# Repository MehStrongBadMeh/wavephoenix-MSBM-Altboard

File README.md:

<h1 align="center">
    WavePhoenix-MSBM-Altboard
</h1>

<p align="center">
    An alternate board design for the WavePhoenix Nintendo WaveBird open-source receiver 
</p>

## Motivation

loopj's Wavephoenix receiver design relies on the RF-Star RF-BM-BG22C3 SoC, which quickly became out-of-stock everywhere, potentially due to people wanting them to make WavePhoenix receivers. So, I set out looking for an alternative. I ended up stumbling upon the [RF-BM-BG22A3](https://www.rfstariot.com/rf-bm-bg22a3-ble5-3-efr32bg22-module_p81.html) which utillizes the same SoC, in a slightly larger package. This means that, if wired properly, it could use the same firmware as the stock Wavephoenix board without modifications. All that was needed was an updated PCB design to utillize this alternate package, and a reworked case to fit the new PCB. The result is slightly bigger than the stock Wavephoenix, but still quite a bit smaller than the original Wavebird receiver.

As a bonus, the pcb antenna in the RF-BM-BG22A3 has great range. I have clocked over 40 feet of range without noticing dropouts.

## Firmware

The WavePhoenix-MSBM-Altboard is identical to the stock firmware of the WavePhoenix, [which can be found here](https://github.com/loopj/wavephoenix).

## Hardware

The hardware for the WavePhoenix-MSBM-Altboard receiver variant is available in the [`hardware/mini-receiver-msbm-altboard`](hardware/mini-receiver-msbm-altboard) directory. The receiver is similar to the reference WavePhoenix receiver other than the replacement of the RF-BM-BG22C3 with the RF-BM-BG22A3.

The hardware folder contains a simple PCB which hosts a [RF-BM-BG22A3](https://www.rfstariot.com/rf-bm-bg22a3-ble5-3-efr32bg22-module_p81.html) module, a pairing button, a status LED, and a JST connector for connecting to a GameCube controller port, as well as a 3D printable case.

- [`case`](hardware/mini-receiver-msbm-altboard/case) - 3D printable case for the receiver
- [`case-usb`](hardware/mini-receiver-msbm-altboard/case-usb) - 3D printable case for a special USB variant of the receiver
- [`gerbers`](hardware/mini-receiver-msbm-altboard/gerbers) - Gerber files for ordering the PCB
- [`KiCad`](hardware/mini-receiver-msbm-altboard/KiCad) - KiCad project files for the PCB

Check out the [`hardware/mini-receiver-msbm-altboard/README.md`](hardware/mini-receiver-msbm-altboard/README.md) for more information on how to build your own receiver based on this hardware variant.

## Special Thanks

- [loopj](https://github.com/loopj) - for creating the original WavePhoenix firmware and hardware that this variant is based on
- [dwillmore](https://github.com/dwillmore) and [unicab369](https://github.com/unicab369) - for giving me a crash course in using KiCad

## License

The hardware is licensed under the [Solderpad Hardware License v2.1](hardware/LICENSE).

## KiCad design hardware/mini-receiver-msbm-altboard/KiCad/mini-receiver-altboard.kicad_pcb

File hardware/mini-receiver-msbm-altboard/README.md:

# WavePhoenix-MSBM-Altboard Mini Receiver

The WavePhoenix-MSBM-Altboard Mini Receiver is a small, low-cost WaveBird receiver replacement based on the original WavePhoenix design. It has been designed to use an alternate chipset but otherwise function identically.

The receiver uses a cheap, off-the-shelf wireless module (the [RF-BM-BG22A3](https://www.rfstariot.com/rf-bm-bg22a3-ble5-3-efr32bg22-module_p81.html)), which can either be hand-wired, or assembled onto a custom PCB.

## Differences

Functionally identical to the stock WavePhoenix other than:

- You need 1x RF-BM-BG22A3 module ([AliExpress](https://www.aliexpress.us/item/3256801502682253.html?spm=a2g0o.detail.1000023.8.191b9Yh19Yh1qO&gatewayAdapt=glo2usa4itemAdapt), [LCSC](https://lcsc.com/product-detail/Bluetooth-Modules_RF-star-RF-BM-BG22A3_C5441203.html?s_z=n_RF-BM-BG22A3), [Tindie](https://www.tindie.com/products/rfstariot/efr32bg22-long-range-bluetooth-wireless-module/)) instead of the RF-BM-BG22C3
- The case has been designed to be used with a standard 1.6mm thick PCB instead of the 1.2mm thickness PCB the stock WavePhoenix was designed around.

## Build Guide

**This guide below is identical to the stock guide ([https://github.com/loopj/wavephoenix/tree/main/hardware/mini-receiver]), other than the differences listed above and some other minor additions**

### Parts

- Assembled Mini Receiver PCB - (see [PCB](#pcb))
- 3D printed case - (see [Case](#case))
- GameCube male connector - ([AliExpress](https://www.aliexpress.us/item/3256804501860592.html), [Alibaba](https://www.alibaba.com/product-detail/NGC-Gamecube-Male-Connector_1600107604838.html), [eBay](https://www.ebay.com/itm/354372477064))
- JST-SH 4-Pin connector with pre-crimped cable - ([AliExpress](https://www.aliexpress.us/item/3256803952186380.html), [Amazon](https://www.amazon.com/dp/B0D9WMLZ7B/))
- 1.5mm PMMA fiber cable - ([AliExpress](https://www.aliexpress.us/item/3256806278563564.html)) *or* 1.5mm diameter x 4mm light pipe - ([AliExpress](https://www.aliexpress.us/item/3256801194682892.html))
- Crimping tool or soldering iron (depending on the your connector type)

### Assembly

- Assemble the JST-SH to GameCube connector cable - (see [Cable](#cable))
- Flash the firmware - (see [Initial Firmware Flashing](#initial-firmware-flashing))
- Insert the GameCube connector into the case until it clicks into place
- Connect the JST-SH connector to the PCB
- Insert the PCB into the case, ensuring the LED and switch are aligned with the holes in the case, it should click into place
- Insert the light pipe into the small hole in the front of the case, if using PMMA fiber for the light pipe, cut it to size first (4mm)
- Insert the 3D printed button into the large hole in the front of the case
- Press the front of the case onto the back of the case

## PCB

The WavePhoenix Mini Receiver PCB is a simple carrier PCB for a RF-BM-BG22C3 module, tact switch, status LED, and a connector for the GameCube controller port.

### Ordering from JLCPCB, PCBWay, etc

You can find the gerber files in the [`gerbers`](gerbers) directory.

Order the PCB with the following settings:

- 2-layer board
- PCB thickness of **1.6mm**
- HASL is fine

### Bill of Materials

- **1x RF-BM-BG22A3 module ([AliExpress](https://www.aliexpress.us/item/3256801502682253.html?spm=a2g0o.detail.1000023.8.191b9Yh19Yh1qO&gatewayAdapt=glo2usa4itemAdapt), [LCSC](https://lcsc.com/product-detail/Bluetooth-Modules_RF-star-RF-BM-BG22A3_C5441203.html?s_z=n_RF-BM-BG22A3), [Tindie](https://www.tindie.com/products/rfstariot/efr32bg22-long-range-bluetooth-wireless-module/))**
- 1x 0805 green LED
- 1x 5x5mm tactile switch
- 1x 4-pin JST-SH connector
- 1x 0402 100Ω resistor (adjust as needed)
- 1x 0402 10uF capacitor
- 1x 0402 0.1uF capacitor

You can find a [Mouser shared cart here](https://www.mouser.com/ProjectManager/ProjectDetail.aspx?AccessID=66aed3ee61). You'll need to source the RF-BM-BG22A3 module separately.

### Hand Assembly

The components should all be hand solderable, the smallest parts being the 0402 capacitors and resistor. If you are struggling with the capacitors, you can omit them, but it is recommended to include them.

I recommend using magnification, and soldering the RF-BM-BG22A3 module first, since the module is hard to solder once the capacitors are in place.

### PCB Assembly Services

If you want to use a PCB assembly service such as JLC PCBA, the CPL file and the BOM file are also found in the [`gerbers`](gerbers) directory.

**Notably, unlike the RF-BM-BG22C3, the RF-BM-BG22A3 qualifies for JLCPCB's Economic assembly, so this variant is considerably cheaper to get pre-assembled versus the stock WavePhoenix.**

## Case

A 3D printable case for the receiver can be found in the [`case`](case) directory. The case is designed to fit the assembled PCB and has a slot for the GameCube connector.

I recommend printing the parts in the default orientation of their STL.

## Case-USB

Oh ho ho, now what do we have here? Some kind of alternative case in the [`case-usb`](case-usb) that is designed to house both a WavePhoenix-MSBM-Altboard and a WaveShare RP2040-Zero. What purpose could that possbily serve? Guess you'll have to tune back in later to find out.

## Cable

> [!TIP]
> The [Fires Custom Controller](https://firescc.com/mod-guides#/diy-custom-cables) custom cable guide, covers the crimping the GameCube connector pins in detail!

Although we are using a 4-pin JST-SH connector, we only actually need 3 wires for the receiver. In the following photos, the ground wire is black, the power wire is red, and the data wire is blue, however the wire colors of pre-made JST cables vary *wildly*, so please check the pinout rather than relying on the wire colors in the photos.

Pin 1 on the JST-SH connector is indicated by a small triangle on the connector housing. In my photos below I have removed the unused wire from pin 4 of the JST-SH connector, but you can also leave it in place if you prefer.

First trim the wires on JST-SH connector cable to 30mm:

Strip a small amount of insulation (~1mm) off the ends of the wires, and crimp the wires to the GameCube connector pins.

Insert the crimped pins into the GameCube connector housing in the following positions:

The “wings” on each pin should face towards the center of the plug, and the pins should be inserted until they click into place.

Next we need to trim off and file down the cable retention tabs on the metal GameCube connector housing:

We can then finally insert the plastic connector into the metal housing:

The complete assembly should look like this:

## Initial Firmware Flashing

> [!NOTE]
> Once you have flashed the bootloader, you can use Bluetooth over-the-air updates to flash future firmware updates!

WavePhoenix receivers have two pieces of software running on them, the *bootloader* and the *application firmware*. The *bootloader* allows us to flash future application updates over Bluetooth, the *application firmware* is the program that handles WaveBird communication.

You can [find the latest bootloader and firmware here](https://github.com/loopj/wavephoenix/releases/latest), the WavePhoenix-MSBM-Altboard mini-receiver needs the `rf-bm-bg22c3` build of the firmware. **(Yes, the RF-BM-BG22A3 is compatible with it)**

The first-time flashing of the firmware requires a debug probe and some special software. If your WavePhoenix board already has the bootloader flashed, you can skip this part.

### Debug Probes

You'll need a SWD debug probe to flash the initial firmware onto the receiver. The debug probe connects to the receiver's SWD pins and allows you to flash the firmware using OpenOCD.

If you don't already have an SWD-capable debug probe, you can build one using a Raspberry Pi Pico. Instructions on how to build a debug probe using a Raspberry Pi Pico can be found in the [Appendix](#pi-pico-debug-probe).

### Pinouts

If you are flashing an assembled Mini Receiver board, the SWD pins are made available in two locations, pads on the back of the board, and via the 4-pin JST-SH connector.

The pinout of the JST-SH connector is as follows:

| Pin | Function | Description              |
| --- | -------- | ------------------------ |
| 1   | GND      | Ground                   |
| 2   | 3.3V     | Power                    |
| 3   | SWDIO    | SWD Data / GameCube Data |
| 4   | SWCLK    | SWD Clock                |

### OpenOCD

To flash the firmware, you'll need to install Arduino's fork of OpenOCD, which adds support for EFR32 Series 2 SoCs.

Prebuilt binaries are available for [Windows](https://downloads.arduino.cc/tools/openocd-0.12.0-arduino1-static-i686-w64-mingw32.tar.bz2), [macOS](https://downloads.arduino.cc/tools/openocd-0.12.0-arduino1-static-x86_64-apple-darwin19.tar.bz2), and [Linux](https://downloads.arduino.cc/tools/openocd-0.12.0-arduino1-static-x86_64-ubuntu16.04-linux-gnu.tar.bz2).

The source for this fork is available on [GitHub here](https://github.com/facchinm/OpenOCD/tree/arduino-0.12.0-rtx5).

### Flashing

Once you have OpenOCD installed, you can flash the bootloader and application firmware using the following commands:

#### Erase the device

First we'll need to do a full device erase:

```bash
# Linux / macOS
openocd -f "interface/cmsis-dap.cfg" \
        -f "target/efm32s2.cfg" \
        -c "init; efm32s2_dci_device_erase; shutdown"
```

```powershell
# Windows (PowerShell)
openocd.exe -f "interface\cmsis-dap.cfg" `
            -f "target\efm32s2.cfg" `
            -c "init; efm32s2_dci_device_erase; shutdown"
```

> [!IMPORTANT]  
> Disconnect then reconnect the debug probe to the receiver before proceeding to the next step.

#### Flash the bootloader

Then we can flash the bootloader:

```bash
# Linux / macOS
openocd -f "interface/cmsis-dap.cfg" \
        -c "transport select swd" \
        -f "target/efm32s2.cfg" \
        -c "init; halt; flash write_image erase bootloader.hex; exit"
```

```powershell
# Windows (PowerShell)
openocd.exe -f "interface\cmsis-dap.cfg" `
            -c "transport select swd" `
            -f "target\efm32s2.cfg" `
            -c "init; halt; flash write_image erase bootloader.hex; exit"
```

> [!TIP]  
> From this point on, you can now use Bluetooth over-the-air updates to flash new application firmware!

#### Flash the application

Since we already have the device wired up, we can also flash the receiver application using SWD:

```bash
# Linux / macOS
openocd -f interface/cmsis-dap.cfg \
        -c "transport select swd" \
        -f target/efm32s2.cfg \
        -c "init; halt; flash write_image erase receiver.hex; exit"
```

```powershell
# Windows
openocd.exe -f interface\cmsis-dap.cfg `
            -c "transport select swd" `
            -f target\efm32s2.cfg `
            -c "init; halt; flash write_image erase receiver.hex; exit"
```

You should now have a fully functional WavePhoenix receiver!

## Usage

### Pairing

WavePhoenix receivers use "virtual pairing" instead of the original WaveBird’s channel wheel. To initiate pairing, press the receiver’s pairing button. The onboard LED will start blinking to indicate the receiver is now in pairing mode. Press and hold X + Y on the WaveBird controller to pair a WaveBird to a receiver. Once pairing is successful, the LED will stop blinking and remain solid.

### Entering Bootloader Mode

You can enter the bootloader for OTA updates in two ways:

1. Press and hold the pairing button for more than 3 seconds, until the LED turns off
2. Press and hold the pairing button while plugging in the receiver

### Upgrading Firmware

You can always find the latest receiver firmware in the [latest release](https://github.com/loopj/wavephoenix/releases/latest) on GitHub. The firmware is available in two formats, a `.gbl` file for over-the-air updates, and a `.hex` file for flashing via SWD.

The mini receiver uses the `rf-bm-bg22c3` build of the firmware, which is specifically designed for the RF-BM-BG22C3 module.

#### Using the WavePhoenix Web App

If you have a computer with Bluetooth or an Android phone, you can use the [WavePhoenix Web App](https://web.wavephoenix.com) in Google Chrome to flash the firmware.

#### Using the WavePhoenix CLI

If you have a computer with Bluetooth, you can also use the [WavePhoenix CLI](https://github.com/loopj/wavephoenix-cli) to flash the firmware:

```bash
wavephoenix flash firmware.gbl
```

#### Using the Simplicity Connect app

Another option is to use the [Simplicity Connect mobile app](https://www.silabs.com/developer-tools/simplicity-connect-mobile-app?tab=downloads) to flash the firmware.

#### Flashing via SWD

You can also always use SWD to re-flash the firmware, as described in the [Initial Firmware Flashing](#initial-firmware-flashing) section.

## Appendix

### Pi Pico Debug Probe

If you have a Raspberry Pi Pico, you can use it as a debug probe to flash WavePhoenix firmware. The Pico is a low-cost (~$4) microcontroller board that can be used as a debug probe with OpenOCD.

Download the latest `debugprobe_on_pico.uf2` from the [Raspberry Pi Debug Probe repo](https://github.com/raspberrypi/debugprobe/releases/latest) and flash it to your Pico by dragging the file onto the Pico's USB drive. Once you have flashed the firmware, the Pico will now be available to use as a debug probe with OpenOCD.

Here's the pinout for SWD programming:

### Flipper Zero Debug

If you are me, then you just used your Flipper Zero as a debug probe, just use the [Dap Link](https://lab.flipper.net/apps/dap_link) app and hook up the pins to the pins you selected in the app for SWC SWD.

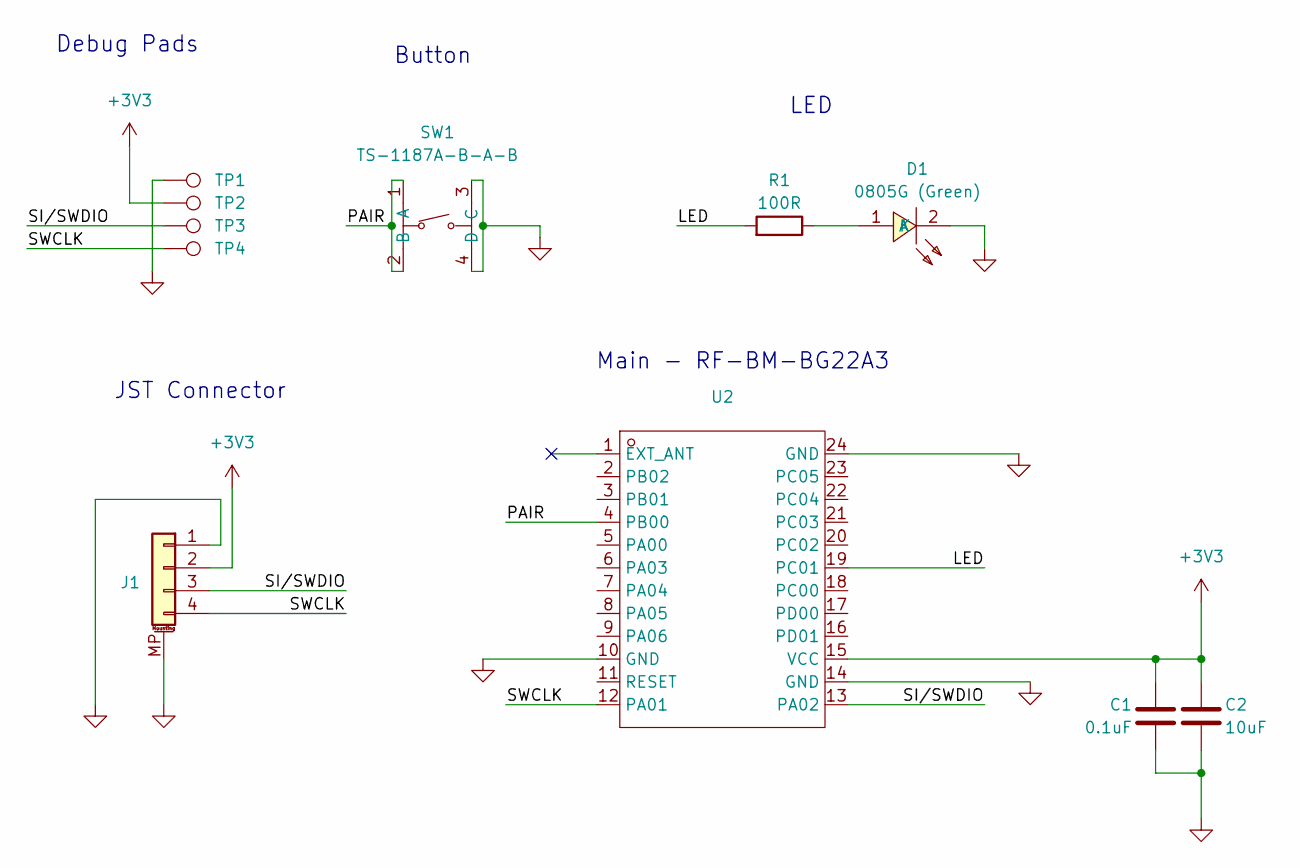
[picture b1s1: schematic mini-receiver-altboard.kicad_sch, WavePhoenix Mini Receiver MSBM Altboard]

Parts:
C1: 0.1uF; C_0402_1005Metric; LCSC C1525
C2: 10uF; C_0402_1005Metric; LCSC C15525
D1: 0805G (Green); LED0805-R-RD; LCSC Part C2297
J1: Conn_01x04_MountingPin; JST_SH_SM04B-SRSS-TB_1x04-1MP_P1.00mm_Horizontal; LCSC C160404
R1: 100R; R_0402_1005Metric; LCSC C25076
SW1: TS-1187A-B-A-B; SW-SMD_4P-L5.1-W5.1-P3.70-LS6.5-TL-2; LCSC Part C318884
TP1: G; TestPoint_Pad_D1.0mm
TP2: V; TestPoint_Pad_D1.0mm
TP3: D; TestPoint_Pad_D1.0mm
TP4: C; TestPoint_Pad_D1.0mm
U2: BULETM-SMD_RF-BM-BG22A1; Manufacturer Part RF-BM-BG22A3; LCSC Part Name EFR32BG22串口透传I2C透传蓝牙模块

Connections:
+3V3: C1.1, C2.1, J1.2, TP2.1, U2.15 (VCC)
/LED: R1.2, U2.19 (PC01)
/PAIR: SW1.1 (A), SW1.2 (B), U2.4 (PB00)
/SI/SWDIO: J1.3, TP3.1, U2.13 (PA02)
/SWCLK: J1.4, TP4.1, U2.12 (PA01)
GND: C1.2, C2.2, D1.2 (K), J1.1, J1.MP (MountPin), SW1.3 (C), SW1.4 (D), TP1.1, U2.10 (GND), U2.14 (GND), U2.24 (GND)
unnamed: D1.1 (A), R1.1

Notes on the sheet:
Debug Pads
Main - RF-BM-BG22A3
LED
Button
JST Connector

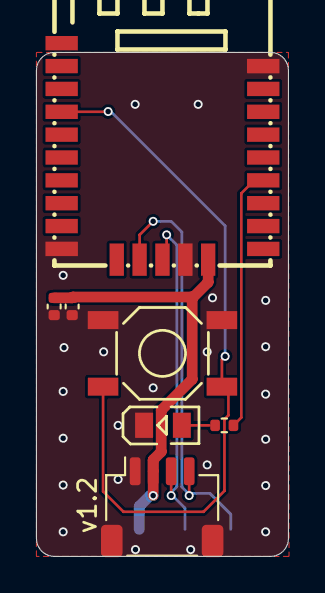
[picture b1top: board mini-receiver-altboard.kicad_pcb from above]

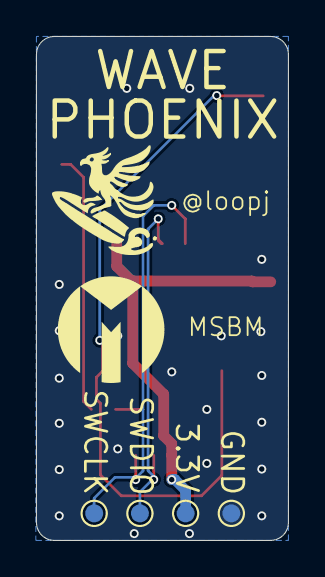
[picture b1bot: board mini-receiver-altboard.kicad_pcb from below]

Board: 2 copper layers, 14.0 x 28.0 mm, 11 parts (4 on the bottom side), 7 nets.

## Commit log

2025-05-27 Add Discord link to README
2025-05-28 Implement stub 'probe device' SI command
2025-05-28 More closely mirror the flag setting behavior of OEM receivers
2025-05-29 Bump internal version
2025-05-30 Fix github action builds
2025-05-30 Add discord announcements for new releases
2025-07-09 Basic support for compiling libwavebird in zephyr
2025-07-09 Ignore all bootloader generated files
2025-07-09 Replace with WavePhoenix-MSBM-Altboard
2025-07-10 Remove workflows
2025-07-10 Fix Readme.md
2025-07-10 Recommend the Arduino fork of openocd
2025-07-11 Fix License Section of Readme
